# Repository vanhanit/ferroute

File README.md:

# ferroute

**Placement-aware, GPU/multi-core accelerated PCB autorouter for KiCad 10 & 11 — written in Rust, with an exact DRC oracle that gates every result.**

*`testdata/boards/demo_2layer.kicad_pcb` (KiCad 10) routed by `ferroute route --allow-move`
with a length rule on `SCL` (rounded meander): 100 % completion, 6 vias, 0 DRC errors in
ferroute's oracle and in KiCad 10.0.8 `kicad-cli pcb drc`. Yellow arrows show unlocked passives
that were nudged; the hatched area is a keep-out.*

## Why another autorouter?

Existing KiCad autorouting stalls on dense boards: nets are committed greedily one at a
time, rip-up passes cycle without memory, and placement is treated as immutable even
when moving one resistor half a millimetre would open a channel. ferroute combines:

* **Negotiated congestion (PathFinder)** on a multi-layer octilinear lattice: all nets
  compete for resources with present + history costs, followed by LNS rip-up rounds.
* **Placement co-optimisation:** explicitly *unlocked* parts (default `R*`, `C*`, `L*`,
  `FB*`; your globs) are nudged within a bound, onto an absolute placement grid
  (`--move-grid`), with 90 deg / 180 deg rotations when that helps routing.
  **Locked footprints never move.**
* **Clean geometry:** 0/45/90 deg tracks, straightened and de-kinked; every connection
  enters its pad along an axis through the centre and ends exactly at the centre; no acid
  traps.
* **Correct by construction, verified anyway:** a *lattice separation theorem* plus exact
  integer predicates; the independent DRC oracle refuses to emit anything it flags.
* **Differential pairs:** coupled routing with constant gap and symmetric fans.
* **Length and delay matching** (`[[match]]`, nested groups, `skew_mm` / `skew_ps`) with
  uniform accordion meanders whose corners are true KiCad arcs.
* **Per-net electrical rules:** current (IPC-2221), impedance, frequency, via limits,
  length; unmet rules are reported, `--strict-rules` fails the run.
* **KiCad custom rules (`.kicad_dru`):** clearance, track width, via, hole, edge, annular
  and diff-pair gap rules, `max` limits, `hole_to_hole`, severities; unsupported conditions
  apply conservatively and are reported.
* **Copper pours:** zones are exact obstacles; other-net pours are refilled around the
  routed copper (`--no-refill-zones` to keep them as obstacles); dog-bone **plane fan-out**
  vias inside the net's own fill.
* **BGA escape planning** and optional **blind / buried / micro vias** (`--via-types`);
  **via-in-pad** (`--allow-via-in-pad`, filled and capped) and `--micro-in-pad` are opt-in.
* **Teardrops** (`--teardrops`, KiCad-native) and **DFM checks** (annular ring, aspect
  ratio, minimum drill, NPTH clearance).
* **Deterministic:** `--seed` replays a run bit-for-bit across thread counts and
  CPU/GPU accelerators (no host-libm in decisions).
* **Portable speed:** `rayon` on every CPU, optional `wgpu` GPU clearance kernels;
  accelerators never change results.
* **Interchange:** lossless `.kicad_pcb` editing (KiCad 6-10 dialects), Specctra
  **DSN export / SES import** (`ferroute dsn`), and the KiCad IPC API in pure Rust (live
  KiCad 10 GUI, headless KiCad 11 `kicad-cli api-server`); never the SWIG bindings.

## Examples

All images are produced by the commands shown (`--svg`), seed 1.

| | |
|---|---|
|  |  |
| `bus_match` with `testdata/rules/bus_match.toml --strict-rules`: nested length matching with rounded meanders, 100 %, 0 DRC | `diff_pair` with `testdata/rules/diff_pair.toml --strict-rules`: coupled pair, constant gap |
|  |  |
| `bga_planes`: BGA fan-out with plane vias, 100 %, 50 vias | synthetic `bga_256_4l` (`gen --suite dense`) with `--via-types through,blind,micro`: 99.5 %, 0 DRC errors (339 of 431 vias are blind/micro: HDI fabrication) |

Read the design in [`docs/ARCHITECTURE_RFC.md`](docs/ARCHITECTURE_RFC.md).

## Quick start

```bash
# Build (Rust toolchain is pinned in rust-toolchain.toml)
cargo build --release -p ferroute-cli          # add --features gpu for wgpu acceleration

# Route a board, letting passives move up to 1.5 mm
./target/release/ferroute route board.kicad_pcb -o board.routed.kicad_pcb \
    --allow-move --max-move 1.5mm --seed 42 --report report.json --svg routed.svg

# Check any board with the exact DRC oracle
./target/release/ferroute drc board.routed.kicad_pcb --fail-on-violation
```

Re-route from scratch, or only some nets (existing copper is otherwise kept as-is):

```bash
ferroute route board.kicad_pcb -o out.kicad_pcb --ripup-all                       # every unlocked track/arc/via
ferroute route board.kicad_pcb -o out.kicad_pcb --ripup-nets 'USB_*' --ripup-nets GND   # net globs, repeatable / comma separated
```

Rip-up deletes only *unlocked* existing tracks, arcs and vias of the selected nets; locked
copper, pours, pads, footprints and no-net copper are never touched, and unknown patterns
are reported as warnings. The ripped copper is gone from the output file, and completion is
reported against the ripped board. Nets that own a copper pour (a zone on any layer) keep
their copper by default, so stitching vias and support tracks keep the pour connected; they
are listed as "kept: owns a copper pour". `--ripup-pour-nets` (or
`[routing] ripup_pour_nets = true`) rips them too, after which pour connectivity may depend
on the router's plane fan-out. Also available as `[routing] ripup = "all"` /
`ripup = ["USB_*"]` in `--rules` (the flags win) and on `ferroute ipc route`.

Or with nothing but Docker and make:

```bash
make dev-image && make build && make e2e && make kicad10-drc
```

### Live KiCad

```bash
# KiCad 10 GUI (enable Preferences → Plugins → "Enable KiCad API")
ferroute ipc probe                 # version + capability negotiation
ferroute ipc route --allow-move    # save → route → reload the open board

# KiCad 11 headless (nightlies)
kicad-cli api-server --socket /tmp/k/api.sock board.kicad_pcb &
ferroute ipc probe --socket ipc:///tmp/k/api.sock --json
ferroute ipc export-svg --socket ipc:///tmp/k/api.sock --out plots/
```

> **KiCad 10 file bridge:** `ipc route` saves the open board, routes the file and reloads
> it. KiCad's undo history is lost, and any edit you make in KiCad while routing runs is
> discarded. A `*.ferroute-bak` backup is written next to the board. Native undoable IPC
> commits are planned (M3).

### Per-net electrical rules

```toml
# rules.toml — ferroute route board.kicad_pcb -o out.kicad_pcb --rules rules.toml
[stackup]
copper_um = 35
outer_dielectric_mm = 0.2
epsilon_r = 4.3

[[net]]                       # IPC-2221: width derived from current (never narrower than class)
nets = ["VBUS", "+5V"]
max_current_a = 2.0

[[net]]                       # impedance → IPC-2141 width; high-speed cost policy
nets = ["USB_D?"]
frequency_mhz = 480
impedance_ohm = 45
match_group = "usb"
skew_max_mm = 0.15
max_vias = 2

[[match]]                     # nested length matching: each pair, then all pairs + CLK
name = "pair0"                # (pair1 defined alike; `groups` globs reference other matches)
nets = ["D0_P", "D0_N"]
skew_mm = 0.1
[[match]]
name = "bus"
groups = ["pair*"]
nets = ["CLK"]
skew_mm = 0.5
```

A `[[match]]` with `by = "delay"` equalises propagation delay instead of length (inner layers
are slower, vias add barrel delay): give its spread as `skew_ps` (not `skew_mm`); optional
`[stackup] board_thickness_mm` (default 1.6) sets the via barrel length.

Selectors are `nets` / `classes` globs. Later rules override only the fields they set.
Nets below `length_min_mm` or outside their group's skew are length-tuned with accordion
meanders (rounded corners as true arcs, uniform, verified by the DRC oracle). Rules that are still not met
are reported, and `--strict-rules` turns them into exit code 2.
See [`testdata/rules/`](testdata/rules) and RFC §4.7.

### Command overview

| Command | Purpose |
|---|---|
| `ferroute route IN -o OUT` | Nudge (opt-in) → route → LNS → DRC gate → write KiCad file (+ JSON report, SVG) |
| `ferroute drc BOARD` | Exact DRC: clearance/shorts, edge, holes, keep-outs, courtyards, sizes, connectivity |
| `ferroute render BOARD -o SVG` | Deterministic SVG with DRC markers and ratsnest |
| `ferroute gen --suite ci -o DIR` | Seeded synthetic benchmark boards (.kicad_pcb + .kicad_pro) |
| `ferroute bench --baseline bench/baseline.json` | Score boards (DRC, completion, wirelength, vias, displacement, runtime) and gate regressions |
| `ferroute dsn export/import-ses` | Specctra DSN export / SES import |
| `ferroute ipc probe/route/export-svg` | KiCad IPC API integration |
| `ferroute info` | Compute backends (CPU threads, GPU adapter) |

Useful `route` flags: `--allow-move`, `--movable 'R*,C*,J5'`, `--exclude 'C1*'`,
`--max-move 2mm`, `--move-grid 0.1mm`, `--no-rotate`, `--pitch 0.4mm`, `--layers F.Cu,B.Cu`,
`--accel auto|cpu|gpu|none`, `--iterations 50`, `--lns-rounds 2`, `--seed N`,
`--rules rules.toml`, `--strict-rules`, `--via-types through,blind,micro`,
`--allow-via-in-pad`, `--teardrops`, `--no-refill-zones`.

## Benchmarks

Measured on a 4-thread Intel Xeon @ 2.1 GHz (CPU backend, `--threads` default), seed 1,
release build. "DRC" is ferroute's oracle (every row is clean; the gate would drop any
violating result). Runtime is wall-clock for the whole pipeline.

`ferroute bench --suite ci --baseline bench/baseline.json` (gate: **PASS**):

| board | layers | mode | completion | vias | wirelength (mm) | time (ms) | DRC |
|---|---|---|---|---|---|---|---|
| ci-s2-small | 2 | nudge | 100 % | 5 | 166.5 | 481 | clean |
| ci-s2-medium | 2 | nudge | 100 % | 15 | 349.3 | 702 | clean |
| ci-s4-medium | 4 | nudge | 100 % | 11 | 418.3 | 1302 | clean |
| demo_2layer | 2 | nudge / fixed | 100 % / 100 % | 6 / 8 | 321.7 / 339.7 | 745 / 444 | clean |
| bus_match | 2 | nudge / fixed | 100 % / 100 % | 3 / 2 | 181.7 / 195.1 | 273 / 198 | clean |
| diff_pair | 2 | nudge / fixed | 100 % / 100 % | 1 / 1 | 109.6 / 109.6 | 43 / 37 | clean |
| bga_planes | 4 | nudge / fixed | 100 % / 100 % | 50 / 50 | 399.3 / 399.3 | 613 / 697 | clean |
| pour_gnd, pour_block, legacy_v9 | 2 | nudge / fixed | 100 % | 0 | 18.2 | < 50 | clean |

`ferroute bench --suite dense` (through-hole vias only, default settings; no gate):

| board | layers | mode | completion | vias | wirelength (mm) | time (s) | DRC |
|---|---|---|---|---|---|---|---|
| qfn_dense_2l | 2 | nudge | 100 % | 34 | 567.8 | 8.8 | clean |
| mixed_8l | 8 | fixed | 100 % | 375 | 5170.6 | 160.5 | clean |
| bga_256_4l | 4 | fixed | 92.5 % | 388 | 1493.0 | 33.4 | clean |
| bga_484_6l | 6 | nudge | 94.2 % | 593 | 1346.4 | 270.5 | clean |

With `--via-types through,blind,micro`, `bga_256_4l` reaches 99.5 % (369/371) in 8 s.
Incomplete connections are reported, never forced: the router prefers an unrouted net to a
violation.

**KiCad 10.0.8 `kicad-cli pcb drc`** (docker `kicad/kicad:10.0.8`, with each board's
`.kicad_pro`, severity error) on routed outputs of `demo_2layer` (nudging), `bus_match`,
`diff_pair`, `bga_planes`, `pour_gnd` and `bga_256_4l` (blind/micro): **0 violations** on
all six; the only unconnected items are the 2 connections `bga_256_4l` reports as unrouted.

CI re-runs the `ci` suite on every PR and fails on any DRC regression, completion drop or
quality regression beyond tolerance (`crates/ferroute-engine/src/score.rs`).

**Versus Freerouting 2.5.0** (same machine, fixed placement, Freerouting 20 passes with
neck-down/fan-out off, hole clearance and pours-as-obstacles set so it honours each board's
rules; method in [`docs/FREEROUTING.md`](docs/FREEROUTING.md); DRC by our oracle; wall times
include Freerouting's JVM/container start and were measured on a shared, loaded machine):

| board | router | completion | DRC errors | vias | wirelength (mm) |
|---|---|---:|---:|---:|---:|
| demo_2layer | ferroute | 100 % | 0 | 8 | 339.7 |
| demo_2layer | Freerouting | 100 % | 0 | 4 | 370.2 |
| bus_match | ferroute | 100 % | 0 | 2 | 195.1 |
| bus_match | Freerouting | 100 % | 0 | 0 | 221.2 |
| qfn_dense_2l | ferroute | 99.3 % | 0 | 56 | 583.4 |
| qfn_dense_2l | Freerouting | 95.7 % | 0 | 31 | 559.9 |
| bga_256_4l | ferroute | 90.6 % | 0 | 373 | 1281.6 |
| bga_256_4l | Freerouting | 62.3 % | 0 | 0 | 1131.0 |

With its default settings Freerouting completes more of the dense boards (100 % / 93.8 %)
but with 95 / 979 DRC errors (narrowed traces, hole clearance, shorts through pours).

## Guarantees and their tests

| Guarantee | How it is enforced |
|---|---|
| No DRC violation introduced | exact oracle as final gate; proptest over hundreds of random dense boards; KiCad 10 `kicad-cli pcb drc` CI lane |
| Locked parts never move; nudges stay in bounds | `BoardEdit::check_invariants` (also re-checked by the KiCad writer); nudger proptests |
| Same seed ⇒ same output | 1/3/4-thread equality tests; frozen PRNG golden values; IEEE-only math in decisions |
| Accelerators never change results | legality tables identical with/without the field |
| Untouched KiCad content is preserved | lossless S-expression edits; byte-identity tests |

## Project status

Pre-1.0. Working end to end: KiCad 10 files in/out, multi-layer routing with
through/blind/buried/micro vias, nudging with rotations, differential pairs, length/delay
matching, `.kicad_dru` rules, copper-pour refill, BGA escape, DSN/SES interchange, IPC
probe and a live file bridge. Known gaps: dense BGAs with through vias only are still
below 100 % (see the dense table), pairs across layers, native undoable IPC commits,
GPU path search (GPU is used for clearance fields only), crosstalk rules and
region-window exact optimisation. See the task board in [`CLAUDE.md`](CLAUDE.md) and the
roadmap in the RFC.

## Contributing

Conventional Commits, `make lint test` green, invariants respected — see
[`CONTRIBUTING.md`](CONTRIBUTING.md). Security issues: [`SECURITY.md`](SECURITY.md).

## Licence

ferroute is **dual-licensed**: [GNU AGPL-3.0-only](LICENSE) for open-source use
(including the network-use clause, §13), or a **commercial licence** for proprietary or
closed-source use — see [`COMMERCIAL.md`](COMMERCIAL.md) and [`NOTICE`](NOTICE).
Boards you route with ferroute are yours; the licence applies to the software.

KiCad is a trademark of the KiCad project; ferroute is an independent project.

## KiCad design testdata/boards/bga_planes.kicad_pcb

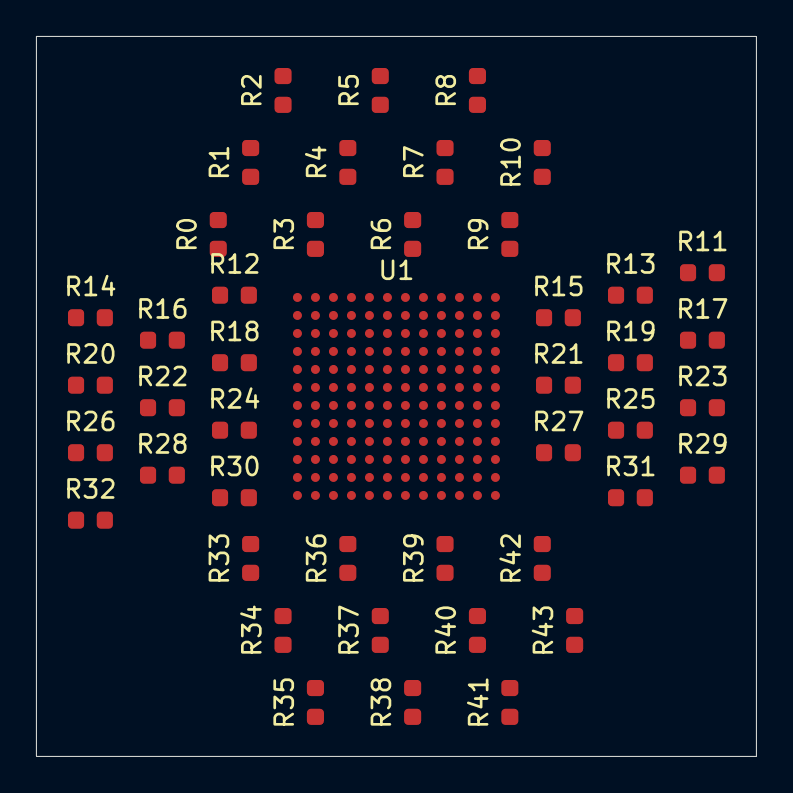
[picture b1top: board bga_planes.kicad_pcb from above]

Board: 4 copper layers, 40.0 x 40.0 mm, 45 parts (0 on the bottom side), 46 nets, no tracks yet.

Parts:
R0, R1, R2, R3, R4, R5, R6, R7, R8, R9, R10, R11, R12, R13, R14, R15, R16, R17, R18, R19, R20, R21, R22, R23, R24, R25, R26, R27, R28, R29, R30, R31, R32, R33, R34, R35, R36, R37, R38, R39, R40, R41, R42, R43: (no value)
U1: (no value)

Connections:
GND: U1.B2, U1.B4, U1.B6, U1.B8, U1.B10, U1.D2, U1.D4, U1.D6, U1.D8, U1.D10, U1.F2, U1.F4, U1.F6, U1.F8, U1.F10, U1.H2, U1.H4, U1.H6, U1.H8, U1.H10, U1.J2, U1.J4, U1.J6, U1.J8, U1.J10
S0: R0.1, U1.A1
S1: R1.1, U1.A2
S2: R2.1, U1.A3
S3: R3.1, U1.A4
S4: R4.1, U1.A5
S5: R5.1, U1.A6
S6: R6.1, U1.A7
S7: R7.1, U1.A8
S8: R8.1, U1.A9
S9: R9.1, U1.A10
S10: R10.1, U1.A11
S11: R11.1, U1.A12
S12: R12.1, U1.B1
S13: R13.1, U1.B12
S14: R14.1, U1.C1
S15: R15.1, U1.C12
S16: R16.1, U1.D1
S17: R17.1, U1.D12
S18: R18.1, U1.E1
S19: R19.1, U1.E12
S20: R20.1, U1.F1
S21: R21.1, U1.F12
S22: R22.1, U1.G1
S23: R23.1, U1.G12
S24: R24.1, U1.H1
S25: R25.1, U1.H12
S26: R26.1, U1.I1
S27: R27.1, U1.I12
S28: R28.1, U1.J1
S29: R29.1, U1.J12
S30: R30.1, U1.K1
S31: R31.1, U1.K12
S32: R32.1, U1.L1
S33: R33.1, U1.L2
S34: R34.1, U1.L3
S35: R35.1, U1.L4
S36: R36.1, U1.L5
S37: R37.1, U1.L6
S38: R38.1, U1.L7
S39: R39.1, U1.L8
S40: R40.1, U1.L9
S41: R41.1, U1.L10
S42: R42.1, U1.L11
S43: R43.1, U1.L12
VCC: U1.C3, U1.C5, U1.C7, U1.C9, U1.C11, U1.E3, U1.E5, U1.E7, U1.E9, U1.E11, U1.G3, U1.G5, U1.G7, U1.G9, U1.G11, U1.I3, U1.I5, U1.I7, U1.I9, U1.I11, U1.K3, U1.K5, U1.K7, U1.K9, U1.K11

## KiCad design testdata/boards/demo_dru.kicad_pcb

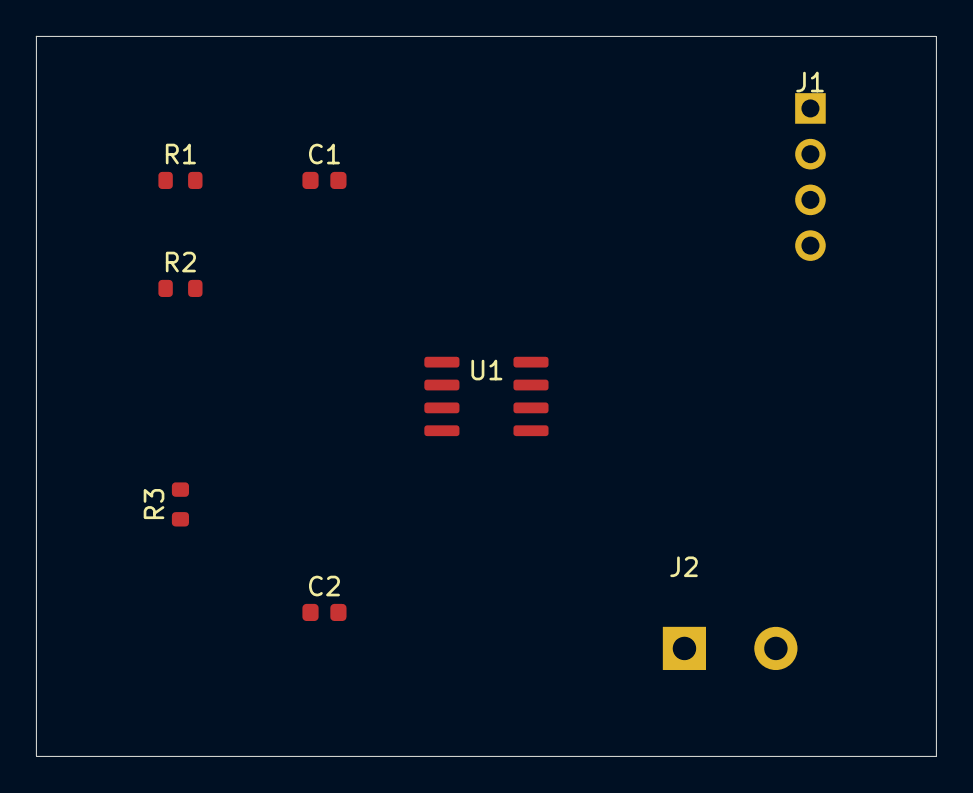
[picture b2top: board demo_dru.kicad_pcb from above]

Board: 2 copper layers, 50.0 x 40.0 mm, 9 parts (1 on the bottom side), 8 nets, no tracks yet.

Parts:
C1: 100n; C_0603_1608Metric
C2: 1u; C_0603_1608Metric
J1: I2C; PinHeader_1x04_P2.54mm_Vertical
J2: OUT; TerminalBlock_bornier-2_P5.08mm
R1, R2: 4.7k; R_0603_1608Metric
R3, R4: 10k; R_0603_1608Metric
U1: SENSOR; SOIC-8_3.9x4.9mm_P1.27mm

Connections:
+3V3: C1.1, J1.1, R1.1, R2.1, R4.1, U1.8
ADDR: R3.1, U1.2
EN: C2.1, U1.3
GND: C1.2, C2.2, J1.4, J2.2, R3.2, U1.4
INT: R4.2, U1.1
OUT: J2.1, U1.7
SCL: J1.3, R2.2, U1.6
SDA: J1.2, R1.2, U1.5

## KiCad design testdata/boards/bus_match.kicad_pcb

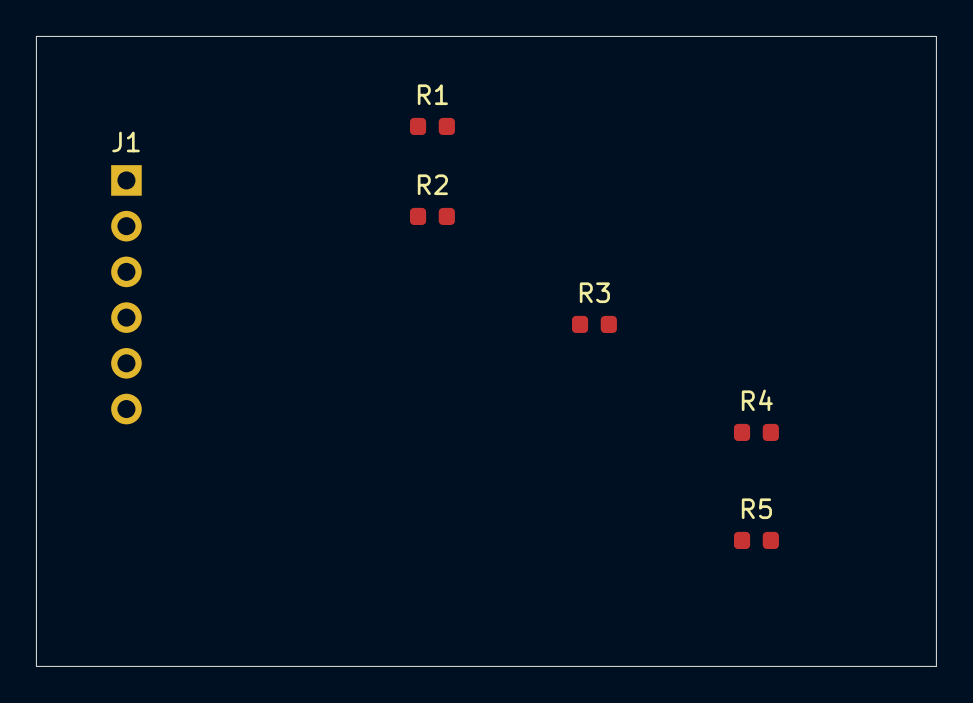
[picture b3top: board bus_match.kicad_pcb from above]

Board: 2 copper layers, 50.0 x 35.0 mm, 6 parts (0 on the bottom side), 6 nets, no tracks yet.

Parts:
J1: (no value)
R1, R2, R3, R4, R5: (no value)

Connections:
CLK: J1.5, R3.1
D0_N: J1.2, R2.1
D0_P: J1.1, R1.1
D1_N: J1.4, R5.1
D1_P: J1.3, R4.1
GND: J1.6, R1.2, R2.2, R3.2, R4.2, R5.2

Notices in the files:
README.md:
License: AGPL-3.0-only
